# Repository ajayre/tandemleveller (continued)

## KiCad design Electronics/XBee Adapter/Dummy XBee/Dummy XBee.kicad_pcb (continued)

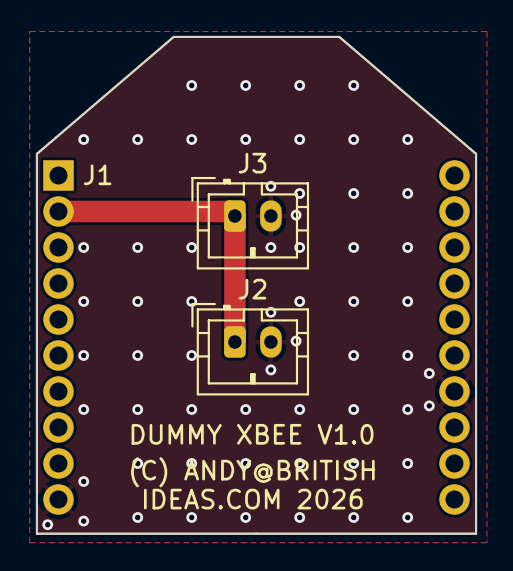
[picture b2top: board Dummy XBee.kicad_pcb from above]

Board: 2 copper layers, 24.4 x 27.6 mm, 3 parts (0 on the bottom side), 2 nets.

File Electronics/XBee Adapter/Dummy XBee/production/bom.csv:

Designator,Footprint,Quantity,Value,LCSC Part #
J1,XBee 3 TH,1,Conn_01x20,
"J2, J3",JST_PH_B2B-PH-K_1x02_P2.00mm_Vertical,2,Conn_01x04,

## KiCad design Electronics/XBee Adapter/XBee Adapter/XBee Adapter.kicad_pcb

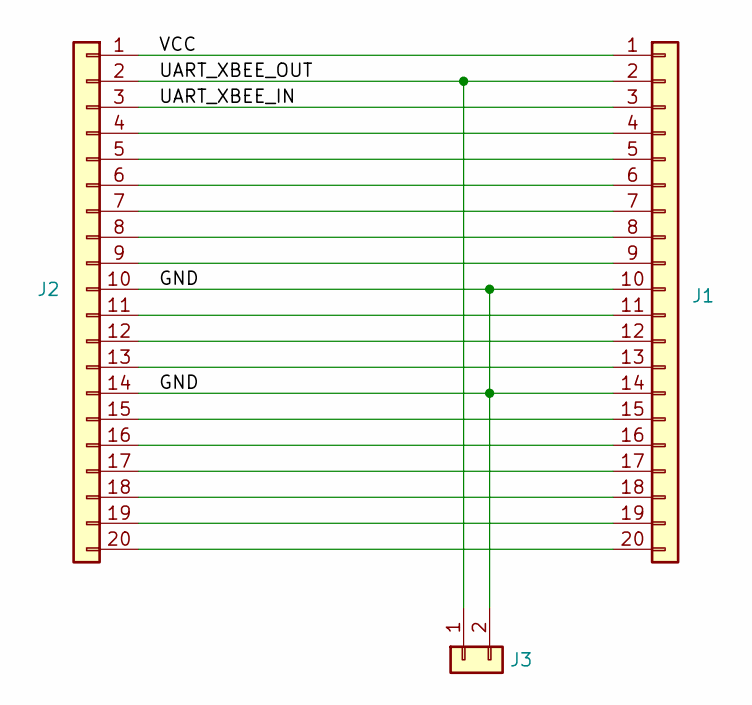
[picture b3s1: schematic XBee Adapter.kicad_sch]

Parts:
J1: Conn_01x20; XBee 3 TH No Outline
J2: Conn_01x20; XBee 3 TH
J3: Conn_01x04; JST_PH_B2B-PH-K_1x02_P2.00mm_Vertical

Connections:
/GND: J1.10, J1.14, J2.10, J2.14, J3.2
/UART_XBEE_IN: J1.3, J2.3
/UART_XBEE_OUT: J1.2, J2.2, J3.1
/VCC: J1.1, J2.1
unnamed: J1.4, J2.4
unnamed: J1.5, J2.5
unnamed: J1.6, J2.6
unnamed: J1.7, J2.7
unnamed: J1.8, J2.8
unnamed: J1.9, J2.9
unnamed: J1.11, J2.11
unnamed: J1.12, J2.12
unnamed: J1.13, J2.13
unnamed: J1.15, J2.15
unnamed: J1.16, J2.16
unnamed: J1.17, J2.17
unnamed: J1.18, J2.18
unnamed: J1.19, J2.19
unnamed: J1.20, J2.20

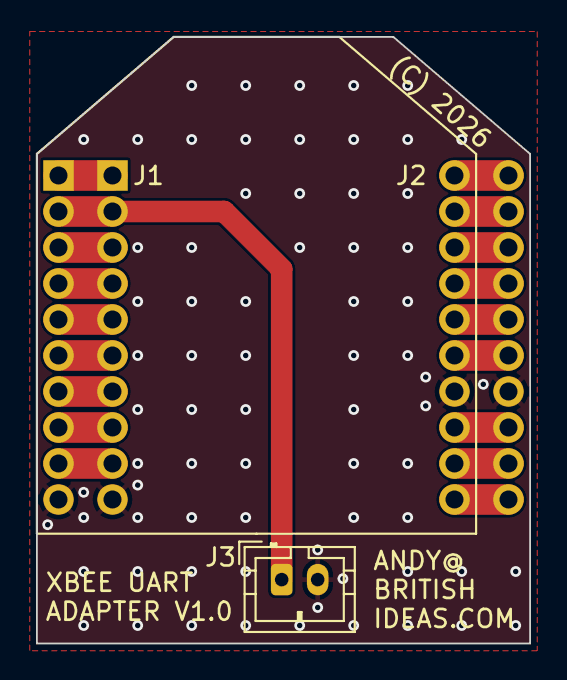
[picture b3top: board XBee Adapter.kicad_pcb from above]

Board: 2 copper layers, 27.4 x 33.7 mm, 3 parts (0 on the bottom side), 19 nets.

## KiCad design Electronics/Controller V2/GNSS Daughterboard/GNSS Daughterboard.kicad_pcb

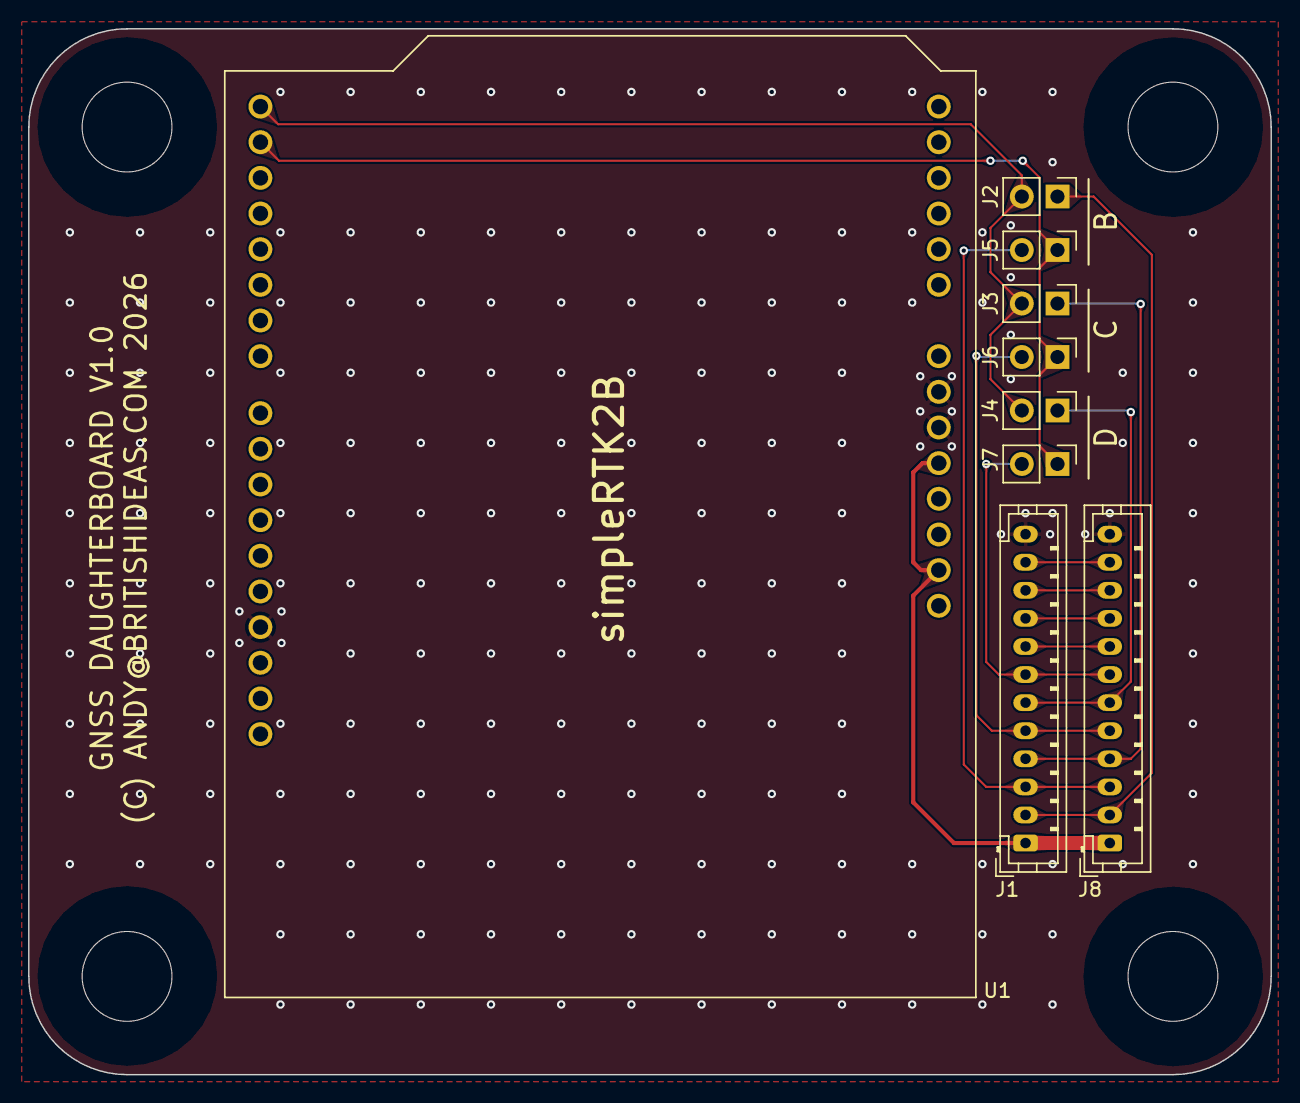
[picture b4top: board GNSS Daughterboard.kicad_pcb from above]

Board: 2 copper layers, 88.5 x 74.5 mm, 13 parts (0 on the bottom side), 14 nets.

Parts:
H1, H2, H3, H4: MountingHole; MountingHole_6.4mm_M6
J1, J8: GNSS; JST_PH_B12B-PH-K_1x12_P2.00mm_Vertical
J2, J3, J4, J5, J6, J7: Conn_01x02; PinHeader_1x02_P2.54mm_Vertical
U1: simpleRTK2B

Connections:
+5V: J1.1, J8.1, U1.20 (IOREF), U1.23 (5V_IN)
/GNSS_B_RX: J1.3, J5.2, J8.3
/GNSS_B_TX: J1.2, J2.1, J8.2
/GNSS_C_RX: J1.5, J6.2, J8.5
/GNSS_C_TX: J1.4, J3.1, J8.4
/GNSS_D_RX: J1.7, J7.2, J8.7
/GNSS_D_TX: J1.6, J4.1, J8.6
/GPIO_G1: J1.8, J8.8
/GPIO_G2: J1.9, J8.9
/GPIO_G3: J1.10, J8.10
/GPIO_G4: J1.11, J8.11
GND: J1.12, J8.12, U1.15 (GND), U1.24 (GND), U1.25 (GND)
unnamed: J2.2, J3.2, J4.2, U1.1 (TX1)
unnamed: J5.1, J6.1, J7.1, U1.2 (RX1)

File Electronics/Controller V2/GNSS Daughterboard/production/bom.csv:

Designator,Footprint,Quantity,Value,LCSC Part #
"H1, H2, H3, H4",MountingHole_6.4mm_M6,4,MountingHole,
"J1, J8",JST_PH_B12B-PH-K_1x12_P2.00mm_Vertical,2,GNSS,
"J2, J3, J4, J5, J6, J7",PinHeader_1x02_P2.54mm_Vertical,6,Conn_01x02,C7494857
U1,simpleRTK2B,1,simpleRTK2B,

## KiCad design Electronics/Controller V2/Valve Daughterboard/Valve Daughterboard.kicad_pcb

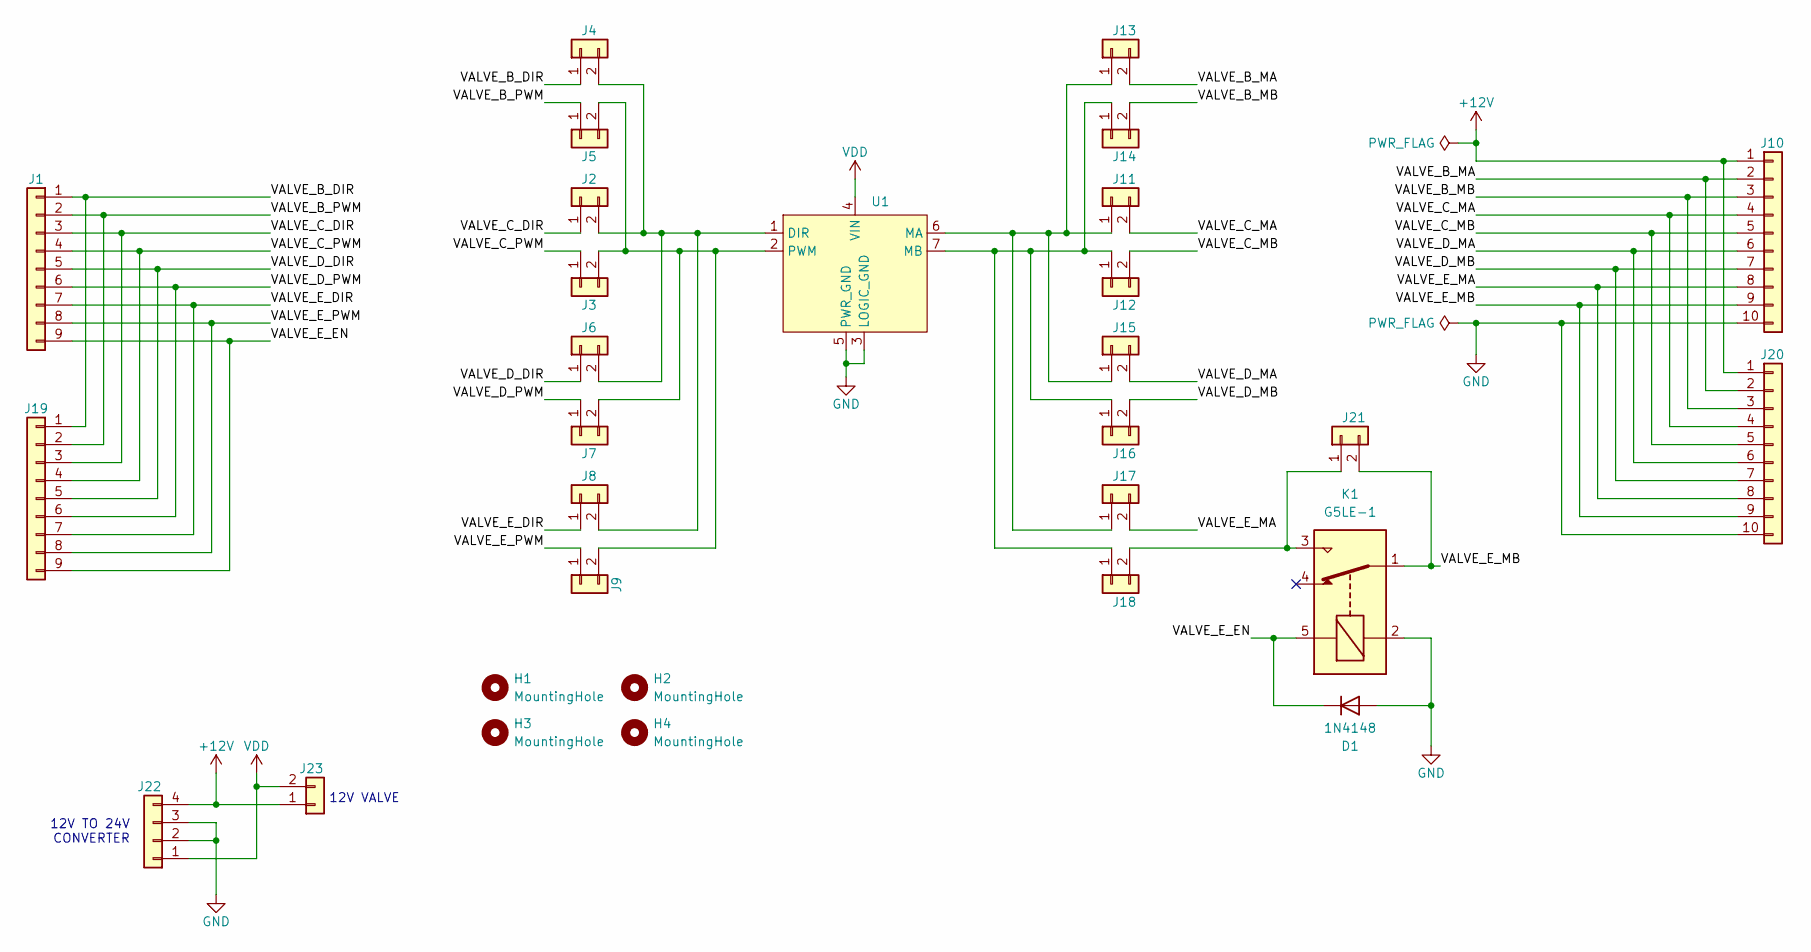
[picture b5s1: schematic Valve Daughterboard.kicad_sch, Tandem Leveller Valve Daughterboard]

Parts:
D1: 1N4148; D_DO-35_SOD27_P7.62mm_Horizontal
H1, H2, H3, H4: MountingHole; MountingHole_6.4mm_M6
J1, J19: Conn_01x08; JST_PH_B9B-PH-K_1x09_P2.00mm_Vertical
J2, J3, J4, J5, J6, J7, J8, J9, J11, J12, J13, J14, J15, J16, J17, J18, J21, J23: Conn_01x02; PinHeader_1x02_P2.54mm_Vertical
J10, J20: Conn_01x10; JST_XH_B10B-XH-A_1x10_P2.50mm_Vertical
J22: Conn_01x04; JST_XH_B4B-XH-A_1x04_P2.50mm_Vertical
K1: G5LE-1; Relay_SPDT_Omron-G5LE-1
U1: MD13S-SUMO

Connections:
+12V: J10.1, J20.1, J22.4, J23.1
/VALVE_B_DIR: J1.1, J4.1, J19.1
/VALVE_B_MA: J10.2, J13.2, J20.2
/VALVE_B_MB: J10.3, J14.2, J20.3
/VALVE_B_PWM: J1.2, J5.1, J19.2
/VALVE_C_DIR: J1.3, J2.1, J19.3
/VALVE_C_MA: J10.4, J11.2, J20.4
/VALVE_C_MB: J10.5, J12.2, J20.5
/VALVE_C_PWM: J1.4, J3.1, J19.4
/VALVE_D_DIR: J1.5, J6.1, J19.5
/VALVE_D_MA: J10.6, J15.2, J20.6
/VALVE_D_MB: J10.7, J16.2, J20.7
/VALVE_D_PWM: J1.6, J7.1, J19.6
/VALVE_E_DIR: J1.7, J8.1, J19.7
/VALVE_E_EN: D1.1 (K), J1.9, J19.9, K1.5
/VALVE_E_MA: J10.8, J17.2, J20.8
/VALVE_E_MB: J10.9, J20.9, J21.2, K1.1
/VALVE_E_PWM: J1.8, J9.1, J19.8
GND: D1.2 (A), J10.10, J20.10, J22.2, J22.3, K1.2, U1.3 (LOGIC_GND), U1.5 (PWR_GND)
unnamed: J2.2, J4.2, J6.2, J8.2, U1.1 (DIR)
unnamed: J3.2, J5.2, J7.2, J9.2, U1.2 (PWM)
unnamed: J11.1, J13.1, J15.1, J17.1, U1.6 (MA)
unnamed: J12.1, J14.1, J16.1, J18.1, U1.7 (MB)
unnamed: J18.2, J21.1, K1.3
VDD: J22.1, J23.2, U1.4 (VIN)

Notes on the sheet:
12V TO 24V CONVERTER
12V VALVE

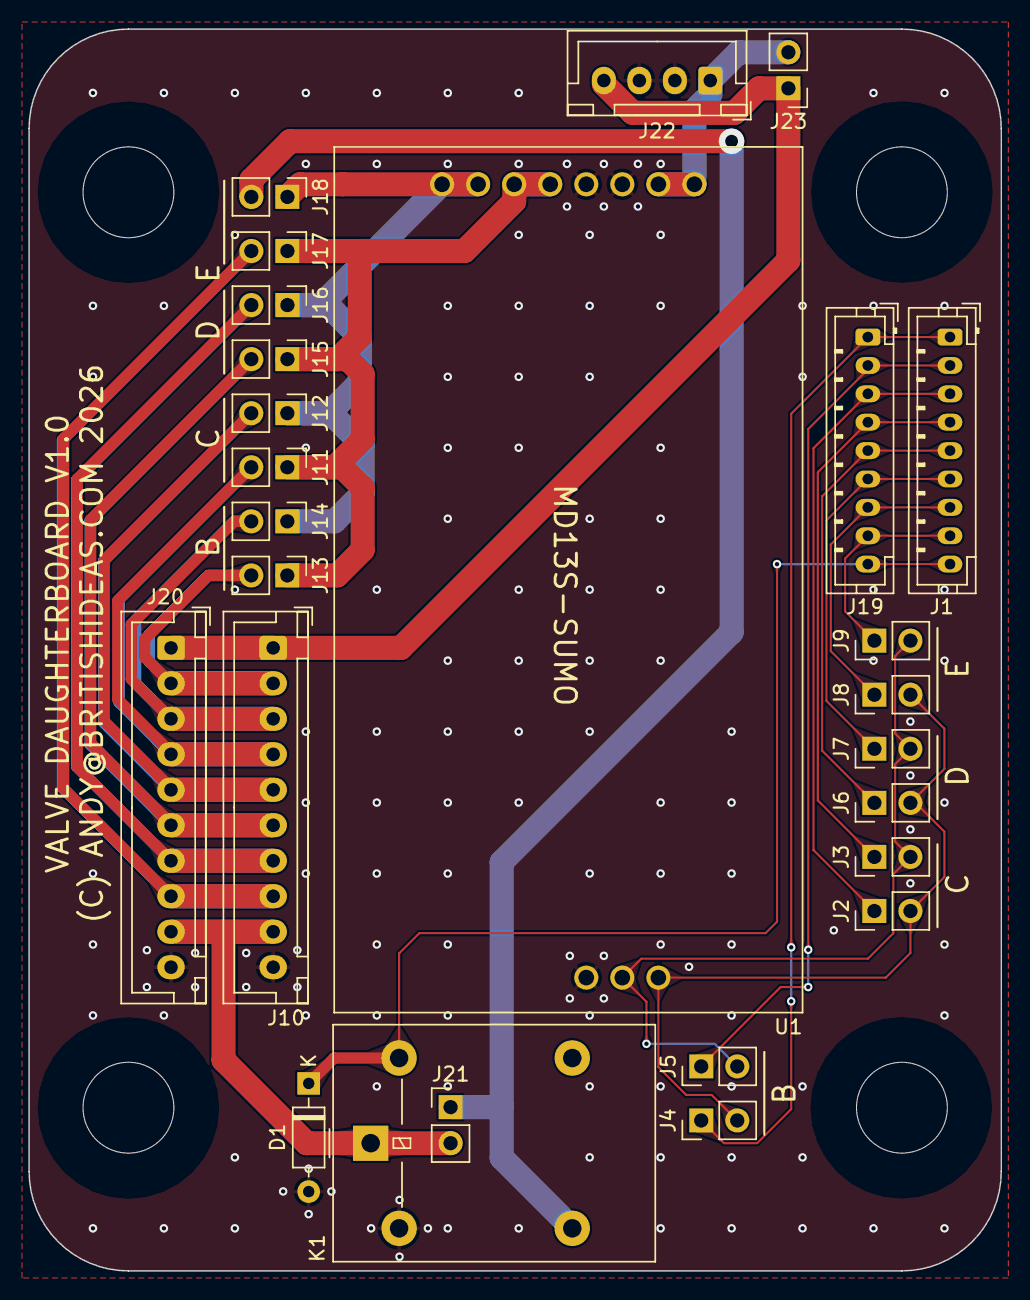
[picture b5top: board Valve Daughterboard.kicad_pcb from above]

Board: 2 copper layers, 68.5 x 87.5 mm, 30 parts (0 on the bottom side), 25 nets.

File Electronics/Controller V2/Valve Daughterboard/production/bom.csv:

Designator,Footprint,Quantity,Value,LCSC Part #
D1,D_DO-35_SOD27_P7.62mm_Horizontal,1,1N4148,
"H1, H2, H3, H4",MountingHole_6.4mm_M6,4,MountingHole,
"J1, J19",JST_PH_B9B-PH-K_1x09_P2.00mm_Vertical,2,Conn_01x08,
"J10, J20",JST_XH_B10B-XH-A_1x10_P2.50mm_Vertical,2,Conn_01x10,
"J11, J12, J13, J14, J15, J16, J17, J18, J2, J21, J23, J3, J4, J5, J6, J7, J8, J9",PinHeader_1x02_P2.54mm_Vertical,18,Conn_01x02,
J22,JST_XH_B4B-XH-A_1x04_P2.50mm_Vertical,1,Conn_01x04,
K1,Relay_SPDT_Omron-G5LE-1,1,G5LE-1,
U1,MD13S-SUMO,1,~,

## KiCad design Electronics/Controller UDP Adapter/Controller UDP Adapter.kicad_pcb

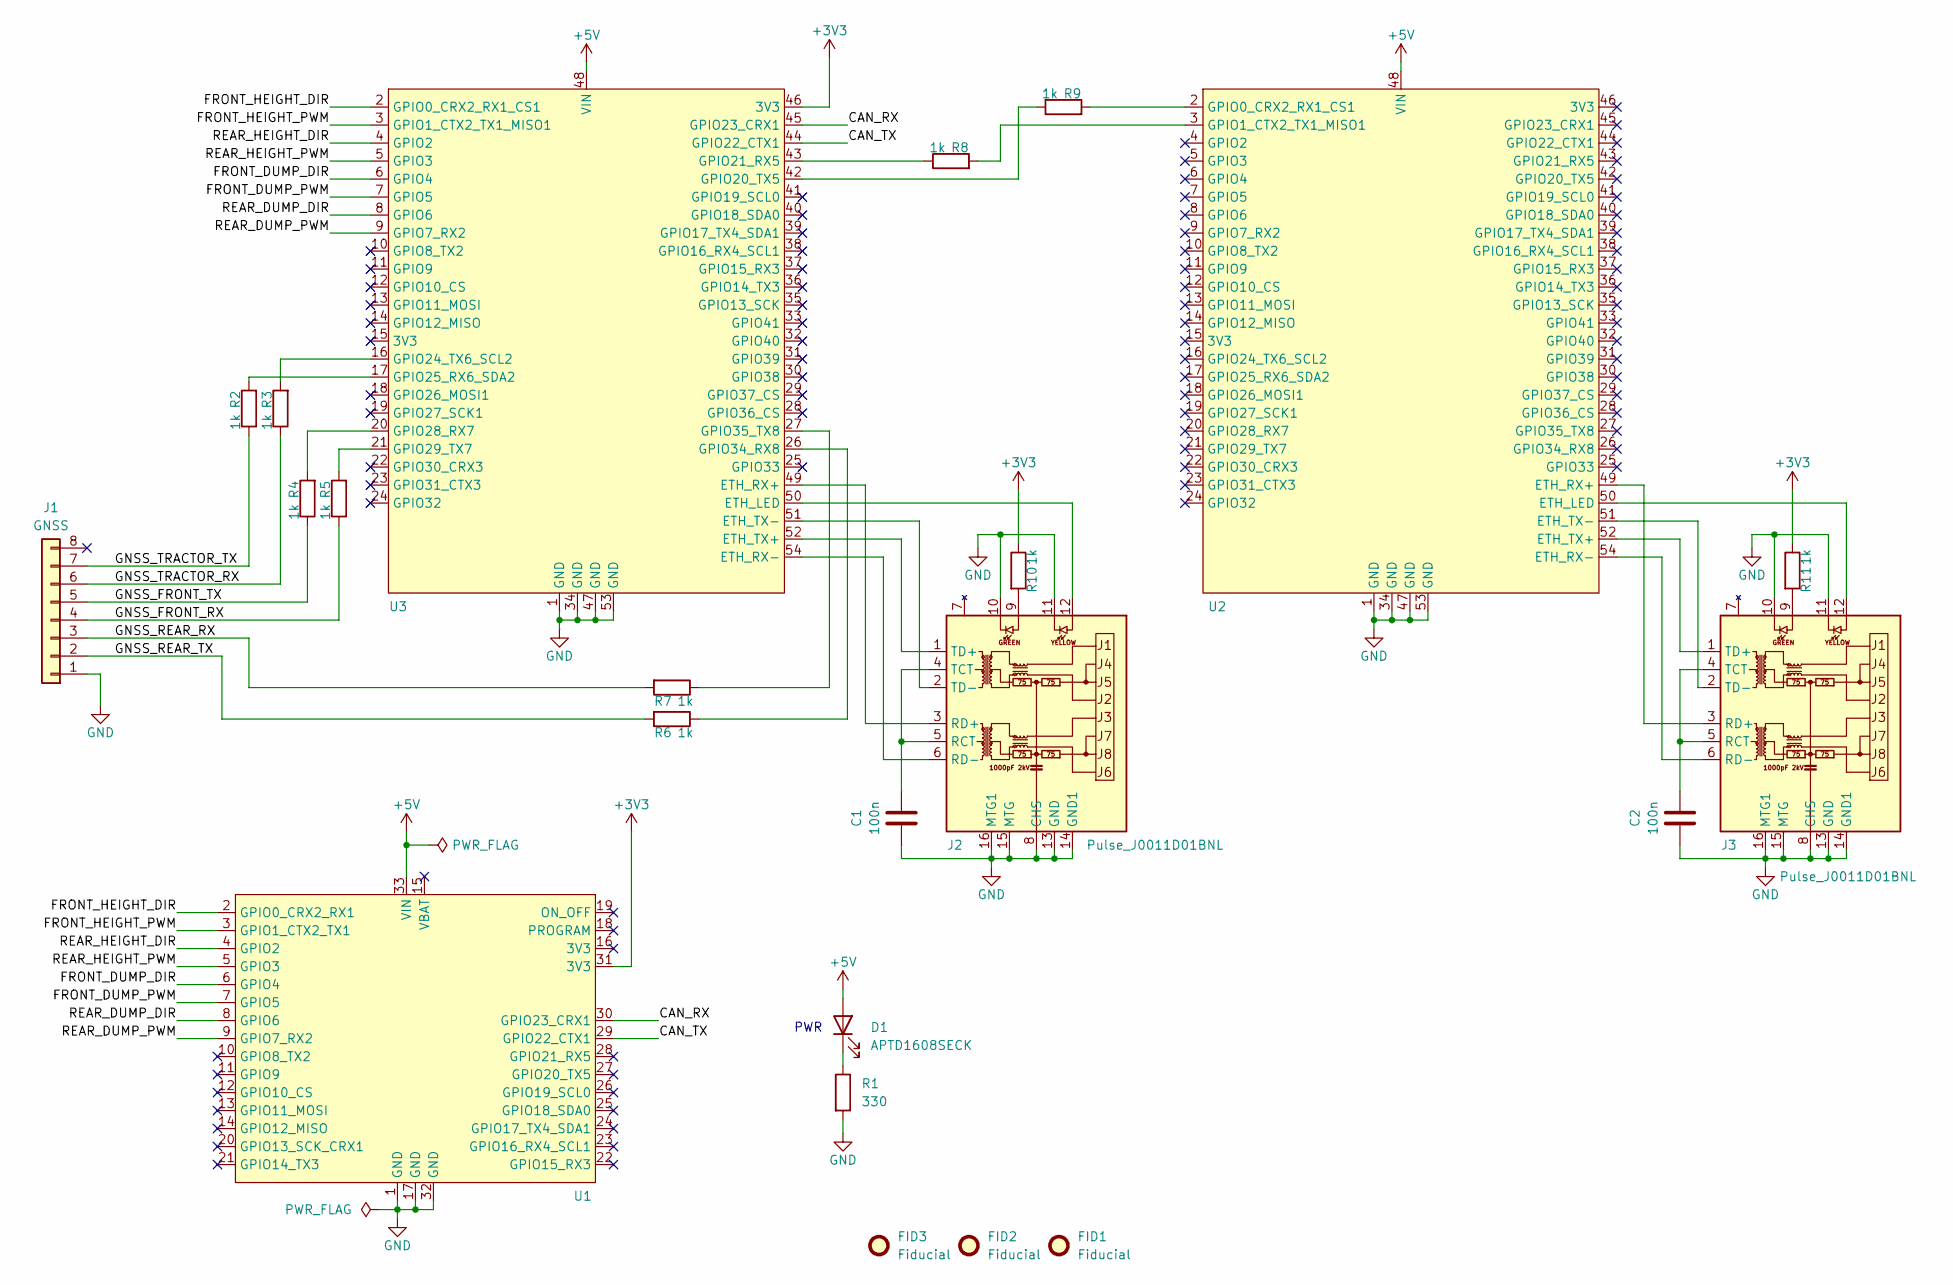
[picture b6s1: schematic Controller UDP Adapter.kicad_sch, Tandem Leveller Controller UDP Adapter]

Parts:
C1, C2: 100n; C_0805_2012Metric; LCSC C1711
D1: APTD1608SECK; D_0603_1608Metric; LCSC C5122084
FID1, FID2, FID3: Fiducial; Fiducial_0.5mm_Mask1mm
J1: GNSS; JST_PH_B8B-PH-K_1x08_P2.00mm_Vertical; LCSC C157974
J2, J3: Pulse_J0011D01BNL; LCSC C581368
R1: 330; R_0805_2012Metric; LCSC C17630
R2, R3, R4, R5, R6, R7, R8, R9, R10, R11: 1k; R_0805_2012Metric; LCSC C17513
U1: Teensy_4.0
U2, U3: Teensy_4.1

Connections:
+3V3: R10.1, R11.1, U1.31 (3V3), U3.46 (3V3)
+5V: D1.2 (A), U1.33 (VIN), U2.48 (VIN), U3.48 (VIN)
/CAN_RX: U1.30 (GPIO23_CRX1), U3.45 (GPIO23_CRX1)
/CAN_TX: U1.29 (GPIO22_CTX1), U3.44 (GPIO22_CTX1)
/FRONT_DUMP_DIR: U1.6 (GPIO4), U3.6 (GPIO4)
/FRONT_DUMP_PWM: U1.7 (GPIO5), U3.7 (GPIO5)
/FRONT_HEIGHT_DIR: U1.2 (GPIO0_CRX2_RX1), U3.2 (GPIO0_CRX2_RX1_CS1)
/FRONT_HEIGHT_PWM: U1.3 (GPIO1_CTX2_TX1), U3.3 (GPIO1_CTX2_TX1_MISO1)
/GNSS_FRONT_RX: J1.4, R5.1
/GNSS_FRONT_TX: J1.5, R4.1
/GNSS_REAR_RX: J1.3, R7.2
/GNSS_REAR_TX: J1.2, R6.2
/GNSS_TRACTOR_RX: J1.6, R3.1
/GNSS_TRACTOR_TX: J1.7, R2.1
/REAR_DUMP_DIR: U1.8 (GPIO6), U3.8 (GPIO6)
/REAR_DUMP_PWM: U1.9 (GPIO7_RX2), U3.9 (GPIO7_RX2)
/REAR_HEIGHT_DIR: U1.4 (GPIO2), U3.4 (GPIO2)
/REAR_HEIGHT_PWM: U1.5 (GPIO3), U3.5 (GPIO3)
GND: C1.1, C2.1, J1.1, J2.8 (CHS), J2.10, J2.11, J2.13 (GND), J2.14 (GND1), J2.15 (MTG), J2.16 (MTG1), J3.8 (CHS), J3.10, J3.11, J3.13 (GND), J3.14 (GND1), J3.15 (MTG), J3.16 (MTG1), R1.2, U1.1 (GND), U1.17 (GND), U1.32 (GND), U2.1 (GND), U2.34 (GND), U2.47 (GND), U2.53 (GND), U3.1 (GND), U3.34 (GND), U3.47 (GND), U3.53 (GND)
unnamed: D1.1 (K), R1.1
unnamed: J2.9, R10.2
unnamed: C1.2, J2.4 (TCT), J2.5 (RCT)
unnamed: J2.3 (RD+), U3.49 (ETH_RX+)
unnamed: J2.6 (RD-), U3.54 (ETH_RX-)
unnamed: J2.1 (TD+), U3.52 (ETH_TX+)
unnamed: J2.2 (TD-), U3.51 (ETH_TX-)
unnamed: J3.9, R11.2
unnamed: C2.2, J3.4 (TCT), J3.5 (RCT)
unnamed: J3.3 (RD+), U2.49 (ETH_RX+)
unnamed: J3.6 (RD-), U2.54 (ETH_RX-)
unnamed: J3.1 (TD+), U2.52 (ETH_TX+)
unnamed: J3.2 (TD-), U2.51 (ETH_TX-)
unnamed: J3.12, U2.50 (ETH_LED)
unnamed: R9.2, U2.2 (GPIO0_CRX2_RX1_CS1)
unnamed: R8.2, U2.3 (GPIO1_CTX2_TX1_MISO1)
unnamed: J2.12, U3.50 (ETH_LED)
unnamed: R9.1, U3.42 (GPIO20_TX5)
unnamed: R8.1, U3.43 (GPIO21_RX5)
unnamed: R3.2, U3.16 (GPIO24_TX6_SCL2)
unnamed: R2.2, U3.17 (GPIO25_RX6_SDA2)
unnamed: R4.2, U3.20 (GPIO28_RX7)
unnamed: R5.2, U3.21 (GPIO29_TX7)
unnamed: R6.1, U3.26 (GPIO34_RX8)
unnamed: R7.1, U3.27 (GPIO35_TX8)

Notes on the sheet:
PWR

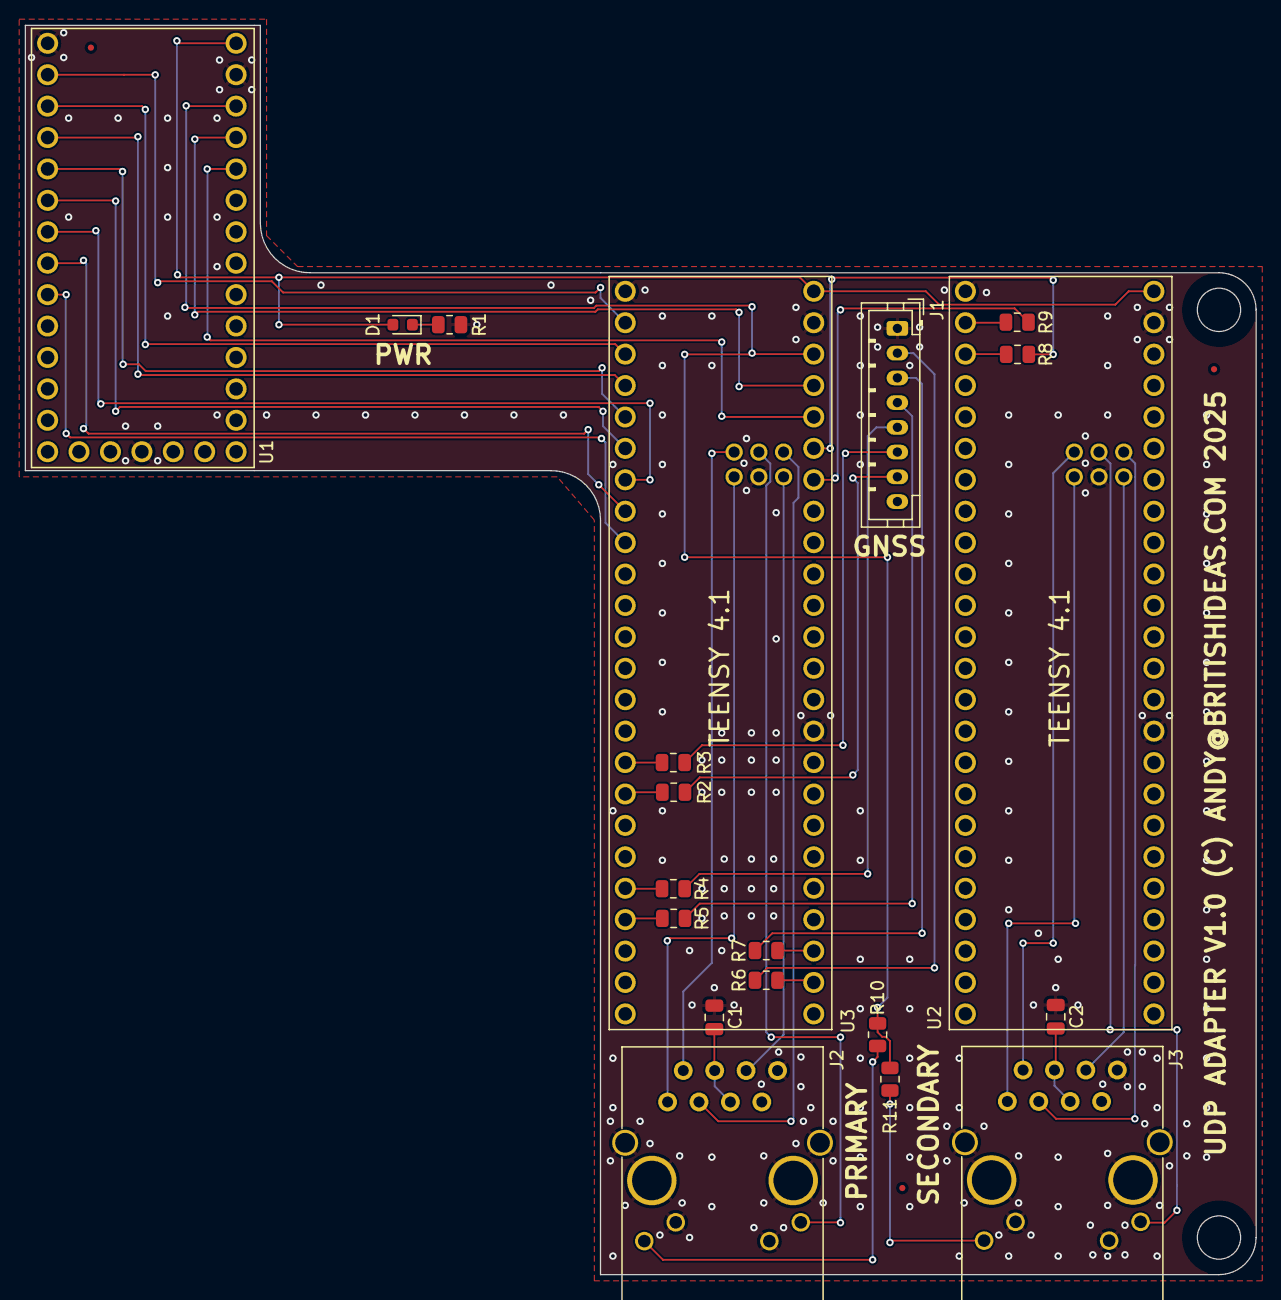
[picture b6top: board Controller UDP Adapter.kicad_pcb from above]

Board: 2 copper layers, 99.5 x 101.0 mm, 23 parts (0 on the bottom side), 44 nets.

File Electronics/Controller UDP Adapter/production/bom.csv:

Designator,Footprint,Quantity,Value,LCSC Part #
"C1, C2",0805,2,100n,C1711
D1,0603,1,APTD1608SECK,C5122084
"FID1, FID2, FID3",Fiducial_0.5mm_Mask1mm,3,Fiducial,
J1,JST_PH_B8B-PH-K_1x08_P2.00mm_Vertical,1,GNSS,C157974
"J2, J3",Pulse_J0011D01BNL,2,Pulse_J0011D01BNL,C581368
R1,0805,1,330,C17630
"R10, R11, R2, R3, R4, R5, R6, R7, R8, R9",0805,10,1k,C17513
U1,Teensy_4.0,1,~,
"U2, U3",Teensy_4.1,2,~,

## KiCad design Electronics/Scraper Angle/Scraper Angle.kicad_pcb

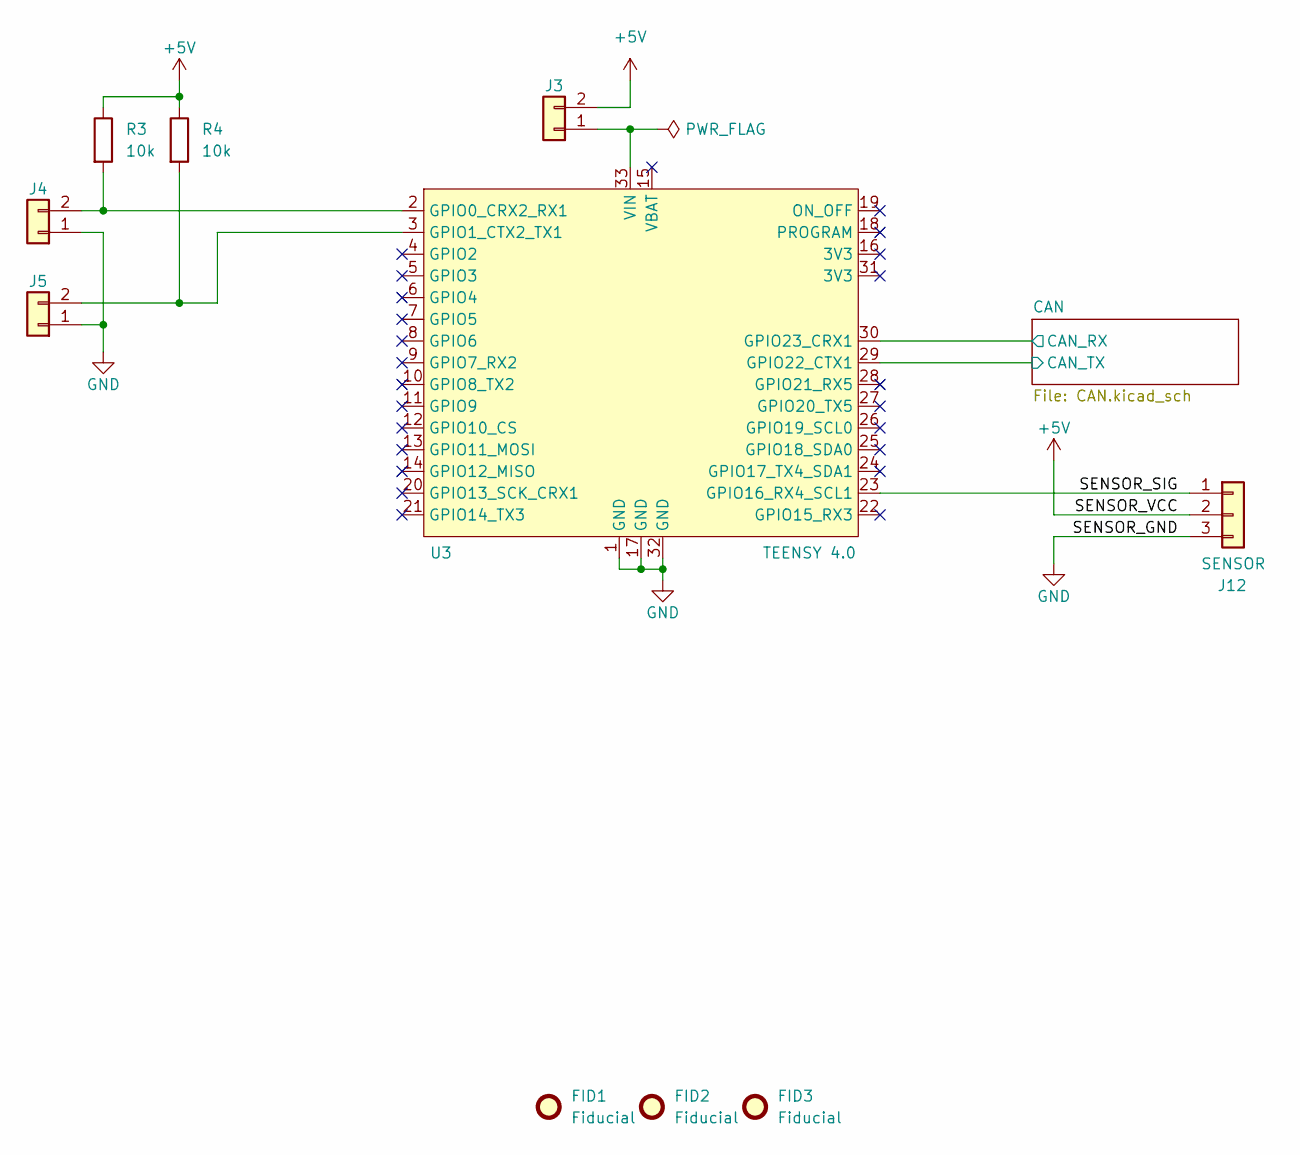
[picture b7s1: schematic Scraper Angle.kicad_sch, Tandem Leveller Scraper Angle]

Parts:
FID1, FID2, FID3: Fiducial; Fiducial_0.5mm_Mask1mm
J3, J4, J5: Conn_01x02; PinHeader_1x02_P2.54mm_Vertical; LCSC C7494857
J12: SENSOR; JST_PH_B3B-PH-K_1x03_P2.00mm_Vertical; LCSC C131339
R3, R4: 10k; R_0805_2012Metric; LCSC C17414
U3: TEENSY 4.0; Teensy_4.0

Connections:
+5V: J3.2, J12.2, R3.1, R4.1; also elsewhere on the board
/CAN/CAN_RX: U3.30 (GPIO23_CRX1); also elsewhere on the board
/CAN/CAN_TX: U3.29 (GPIO22_CTX1); also elsewhere on the board
/SENSOR_SIG: J12.1, U3.23 (GPIO16_RX4_SCL1)
GND: J4.1, J5.1, J12.3, U3.1 (GND), U3.17 (GND), U3.32 (GND); also elsewhere on the board
unnamed: J3.1, U3.33 (VIN)
unnamed: J4.2, R3.2, U3.2 (GPIO0_CRX2_RX1)
unnamed: J5.2, R4.2, U3.3 (GPIO1_CTX2_TX1)

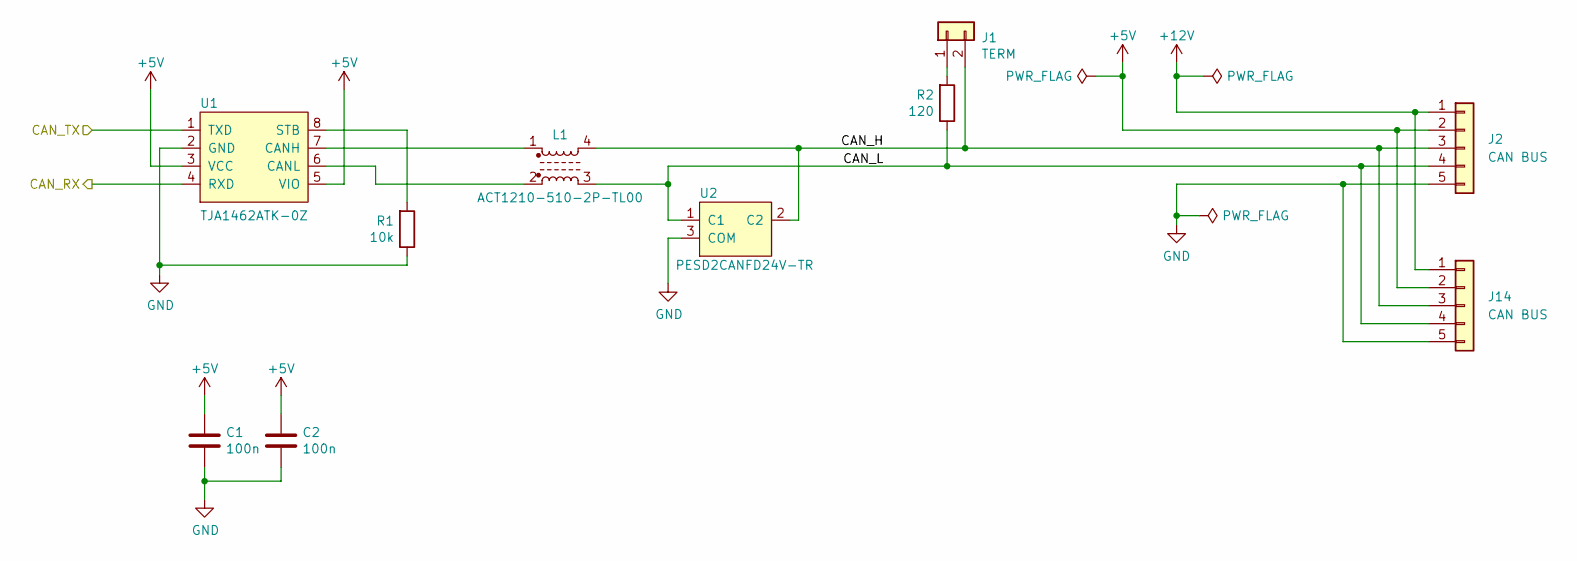
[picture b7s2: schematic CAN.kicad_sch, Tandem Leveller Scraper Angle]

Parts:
C1, C2: 100n; C_0805_2012Metric; LCSC C1711
J1: TERM; PinHeader_1x02_P2.54mm_Vertical; LCSC C7494857
J2, J14: CAN BUS; JST_PH_B5B-PH-K_1x05_P2.00mm_Vertical; LCSC C157993
L1: ACT1210-510-2P-TL00; LCSC C95572
R1: 10k; R_0805_2012Metric; LCSC C17414
R2: 120; R_0805_2012Metric; LCSC C17437
U1: TJA1462ATK-0Z; HVSON8_0_65mm; LCSC C3229259
U2: PESD2CANFD24V-TR; SOT-23; LCSC C552486

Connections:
+5V: C1.1, C2.1, J2.2, J14.2, U1.3 (VCC), U1.5 (VIO); also elsewhere on the board
+12V: J2.1, J14.1
/CAN/CAN_H: J1.2, J2.3, J14.3, L1.4, U2.2 (C2)
/CAN/CAN_L: J2.4, J14.4, L1.3, R2.1, U2.1 (C1)
/CAN/CAN_RX: U1.4 (RXD); also elsewhere on the board
/CAN/CAN_TX: U1.1 (TXD); also elsewhere on the board
GND: C1.2, C2.2, J2.5, J14.5, R1.1, U1.2 (GND), U2.3 (COM); also elsewhere on the board
unnamed: J1.1, R2.2
unnamed: L1.1, U1.7 (CANH)
unnamed: L1.2, U1.6 (CANL)
unnamed: R1.2, U1.8 (STB)

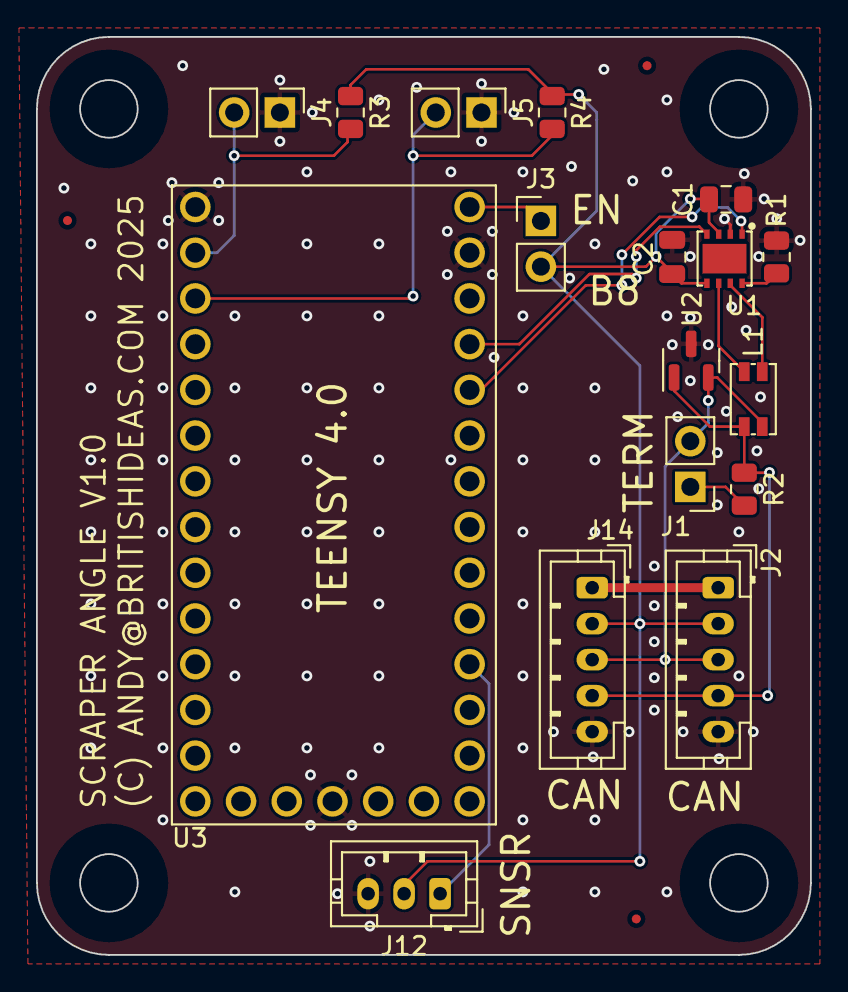
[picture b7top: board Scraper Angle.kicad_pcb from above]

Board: 2 copper layers, 43.0 x 51.0 mm, 20 parts (0 on the bottom side), 15 nets.

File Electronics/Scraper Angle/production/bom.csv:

Designator,Footprint,Quantity,Value,LCSC Part #
"C1, C2",0805,2,100n,C1711
"FID1, FID2, FID3",Fiducial_0.5mm_Mask1mm,3,Fiducial,
J1,PinHeader_1x02_P2.54mm_Vertical,1,TERM,C7494857
J12,JST_PH_B3B-PH-K_1x03_P2.00mm_Vertical,1,SENSOR,C131339
"J14, J2",JST_PH_B5B-PH-K_1x05_P2.00mm_Vertical,2,CAN BUS,C157993
"J3, J4, J5",PinHeader_1x02_P2.54mm_Vertical,3,Conn_01x02,C7494857
L1,ACT1210-510-2P-TL00,1,ACT1210-510-2P-TL00,C95572
"R1, R3, R4",0805,3,10k,C17414
R2,0805,1,120,C17437
U1,HVSON8_0_65mm,1,TJA1462ATK-0Z,C3229259
U2,SOT-23,1,PESD2CANFD24V-TR,C552486
U3,Teensy_4.0,1,TEENSY 4.0,

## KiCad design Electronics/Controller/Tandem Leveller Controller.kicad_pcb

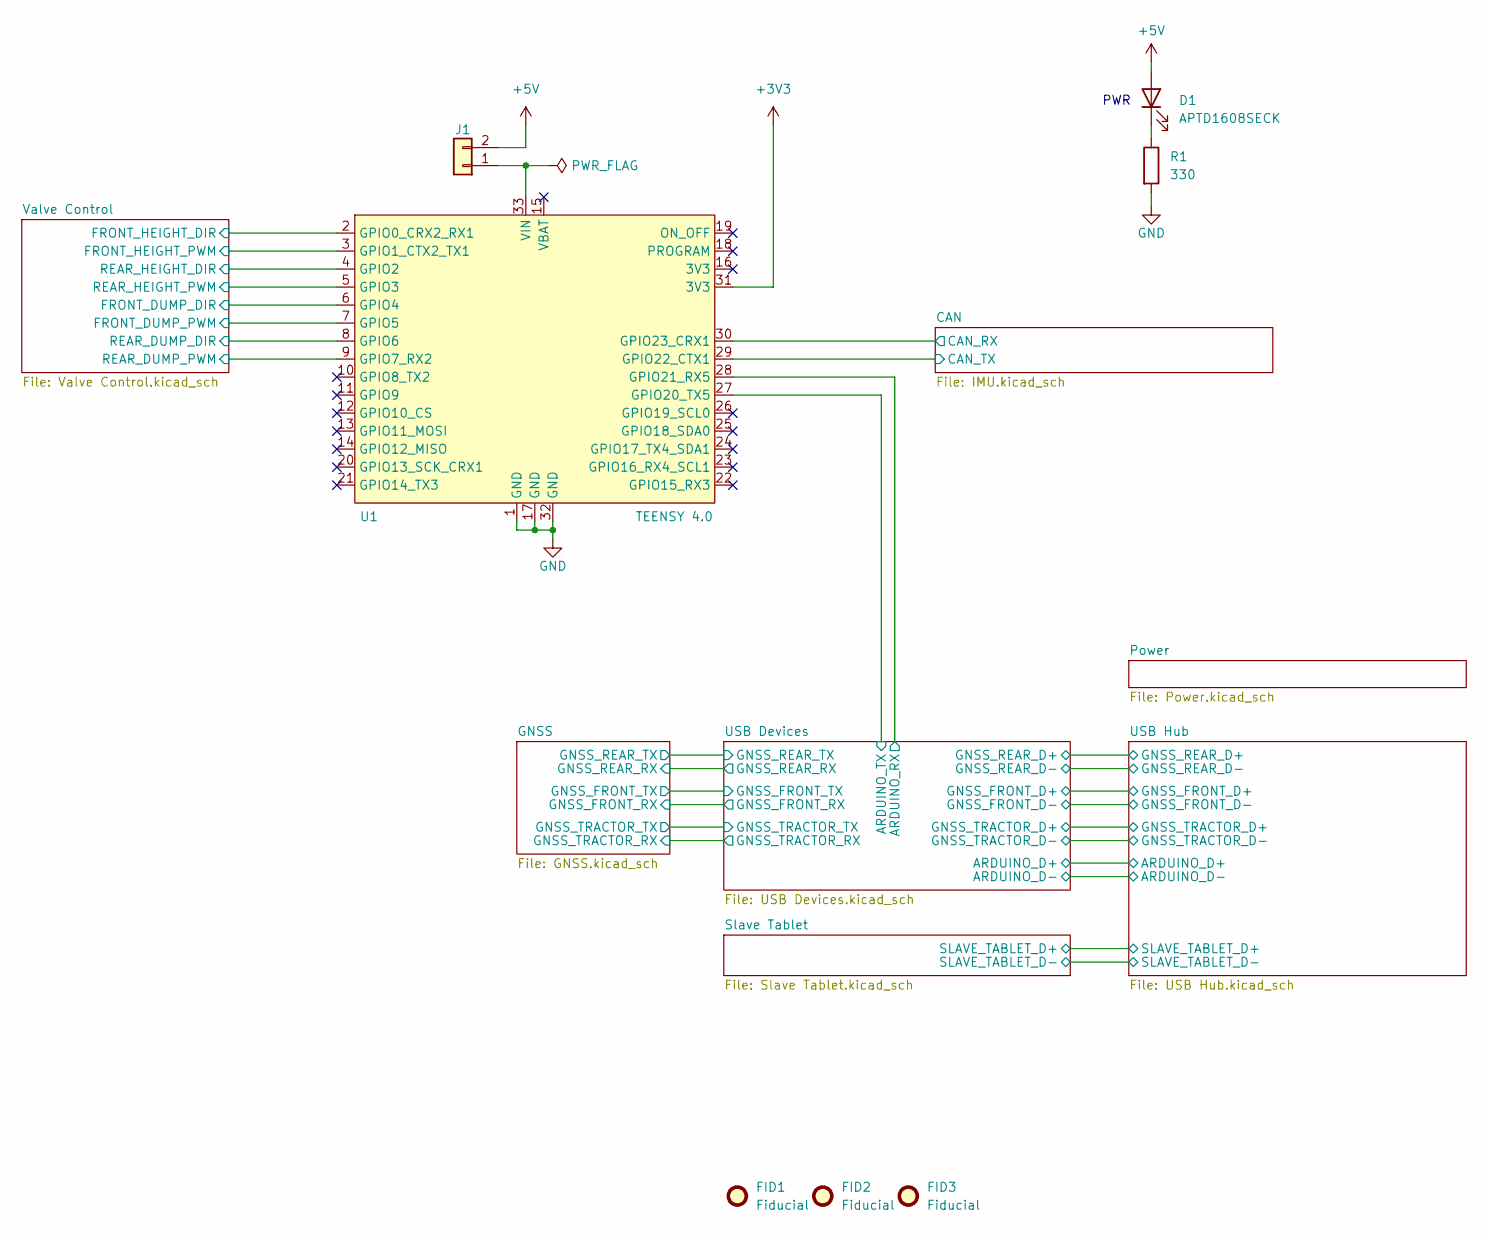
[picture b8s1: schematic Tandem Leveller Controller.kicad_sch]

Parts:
D1: APTD1608SECK; D_0603_1608Metric; LCSC C5879220
FID1, FID2, FID3: Fiducial; Fiducial_0.5mm_Mask1mm
J1: Conn_01x02; PinHeader_1x02_P2.54mm_Vertical; LCSC C7494857
R1: 330; R_0805_2012Metric; LCSC C17630
U1: TEENSY 4.0; Teensy_4.0

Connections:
+3V3: U1.31 (3V3); also elsewhere on the board
+5V: D1.2 (A), J1.2; also elsewhere on the board
/CAN/CAN_RX: U1.30 (GPIO23_CRX1); also elsewhere on the board
/CAN/CAN_TX: U1.29 (GPIO22_CTX1); also elsewhere on the board
/USB Devices/ARDUINO_RX: U1.28 (GPIO21_RX5); also elsewhere on the board
/USB Devices/ARDUINO_TX: U1.27 (GPIO20_TX5); also elsewhere on the board
/Valve Control/FRONT_DUMP_DIR: U1.6 (GPIO4); also elsewhere on the board
/Valve Control/FRONT_DUMP_PWM: U1.7 (GPIO5); also elsewhere on the board
/Valve Control/FRONT_HEIGHT_DIR: U1.2 (GPIO0_CRX2_RX1); also elsewhere on the board
/Valve Control/FRONT_HEIGHT_PWM: U1.3 (GPIO1_CTX2_TX1); also elsewhere on the board
/Valve Control/REAR_DUMP_DIR: U1.8 (GPIO6); also elsewhere on the board
/Valve Control/REAR_DUMP_PWM: U1.9 (GPIO7_RX2); also elsewhere on the board
/Valve Control/REAR_HEIGHT_DIR: U1.4 (GPIO2); also elsewhere on the board
/Valve Control/REAR_HEIGHT_PWM: U1.5 (GPIO3); also elsewhere on the board
GND: R1.2, U1.1 (GND), U1.17 (GND), U1.32 (GND); also elsewhere on the board
unnamed: D1.1 (K), R1.1
unnamed: J1.1, U1.33 (VIN)

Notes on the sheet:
PWR
